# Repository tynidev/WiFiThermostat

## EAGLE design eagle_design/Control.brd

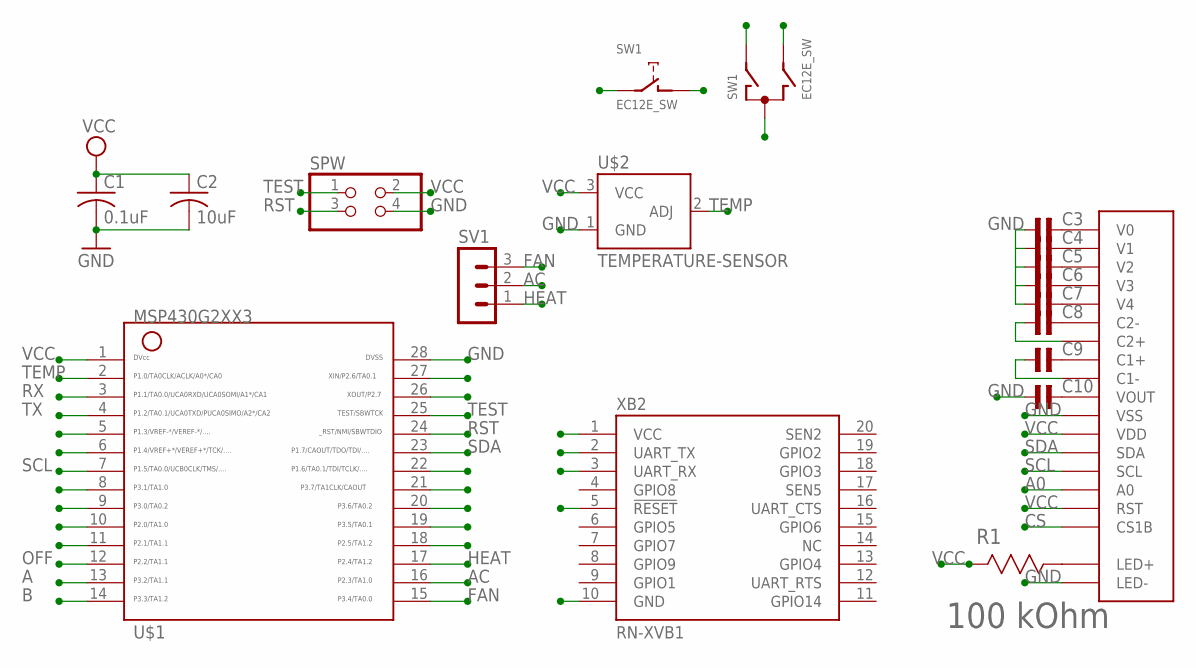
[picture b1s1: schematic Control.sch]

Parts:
C1: 0.1uF; C0603K
C2: 10uF; C0603K
C3, C4, C5, C6, C7, C8, C9, C10: C-NP-SMD-0603; C-0603
R1: 100 kOhm; RESC1608X60N
SPW: PINHD-2X2; 2X02
SV1: MA03-1
SW1: EC12E_SW; ALPS_EC12E_SW
U$1: G2XX3---PW28; PW28
U$2: TEMPERATURE-SENSOR; TO-92
U$3: NHD-C12832A1Z-FSW-FBW-3V3
XB2: RN-XVB1; XBEE

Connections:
A: SW1.B, U$1.13
A0: U$1.8, U$3.15 (A0)
AC: SV1.2, U$1.16
B: SW1.A, U$1.14
CS: U$1.9, U$3.17 (CS1B)
FAN: SV1.3, U$1.15
GND: C1.2, C2.2, C3.1, C4.1, C5.1, C6.1, C7.1, C10.1, SPW.4, SW1.C, U$1.28, U$2.1 (GND), U$3.11 (VSS), U$3.K (LED-), XB2.10 (GND)
HEAT: SV1.1, U$1.17
unnamed: C3.2, U$3.1 (V0)
unnamed: C4.2, U$3.2 (V1)
unnamed: C5.2, U$3.3 (V2)
unnamed: C6.2, U$3.4 (V3)
unnamed: C7.2, U$3.5 (V4)
unnamed: C8.2, U$3.6 (C2-)
unnamed: C9.2, U$3.8 (C1+)
unnamed: C8.1, U$3.7 (C2+)
unnamed: C10.2, U$3.10 (VOUT)
unnamed: C9.1, U$3.9 (C1-)
unnamed: R1.1 (R1), U$3.A (LED+)
OFF: SW1.E (2), U$1.12
P1_3: U$1.5
P1_4: U$1.6
P1_6: U$1.22
P2_0: U$1.10
P2_1: U$1.11
P2_5: U$1.18
P2_6: U$1.27
P2_7: U$1.26
P3_5: U$1.19
P3_6: U$1.20
P3_7: U$1.21
RST: SPW.3, U$1.24
RX: U$1.3, XB2.2 (UART_TX)
SCL: U$1.7, U$3.14 (SCL)
SDA: U$1.23, U$3.13 (SDA)
TEMP: U$1.2, U$2.2 (ADJ)
TEST: SPW.1, U$1.25
TX: U$1.4, XB2.3 (UART_RX)
VCC: C1.1, C2.1, R1.2 (R2), SPW.2, SW1.D (1), U$1.1, U$2.3 (VCC), U$3.12 (VDD), U$3.16 (RST), XB2.1 (VCC), XB2.5 (!RESET)

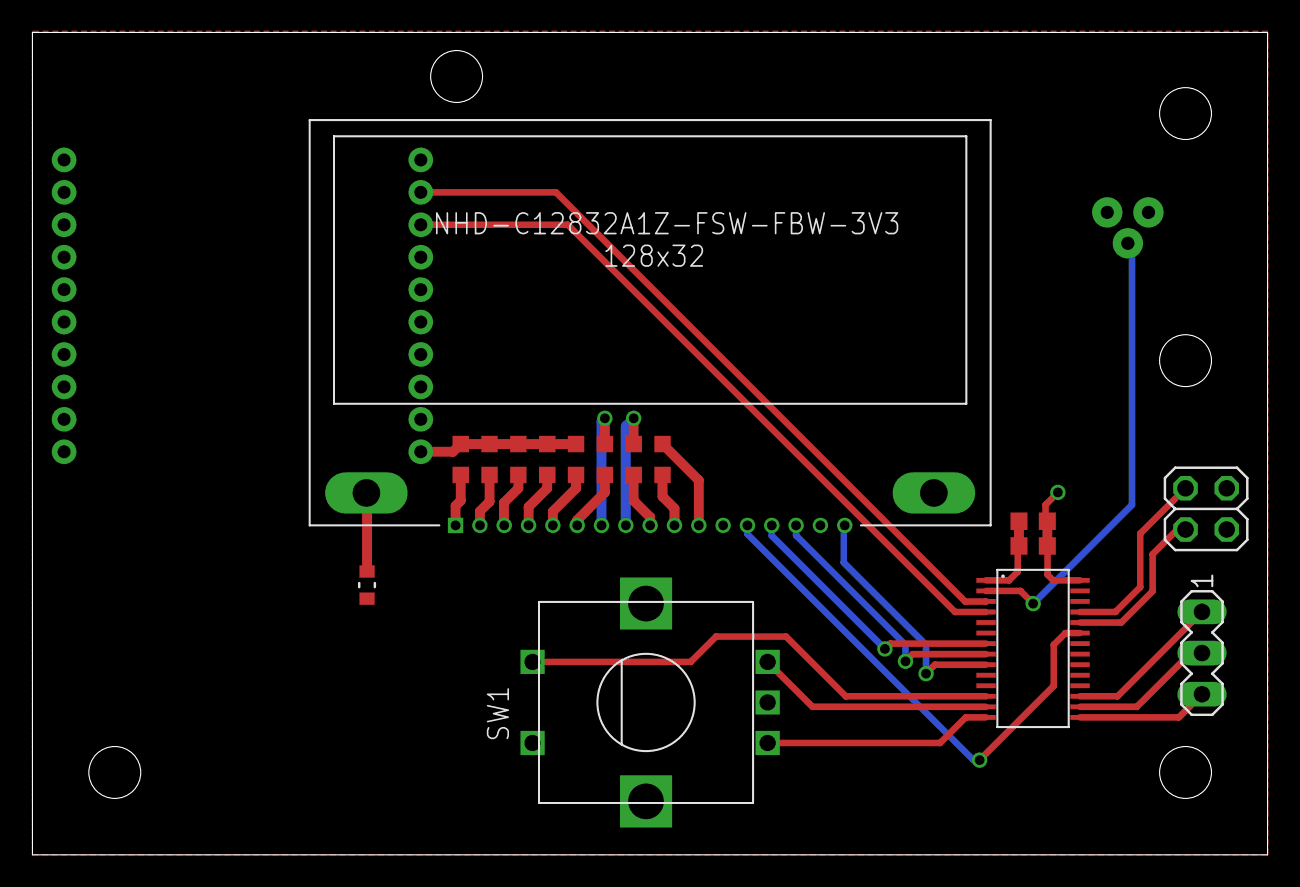
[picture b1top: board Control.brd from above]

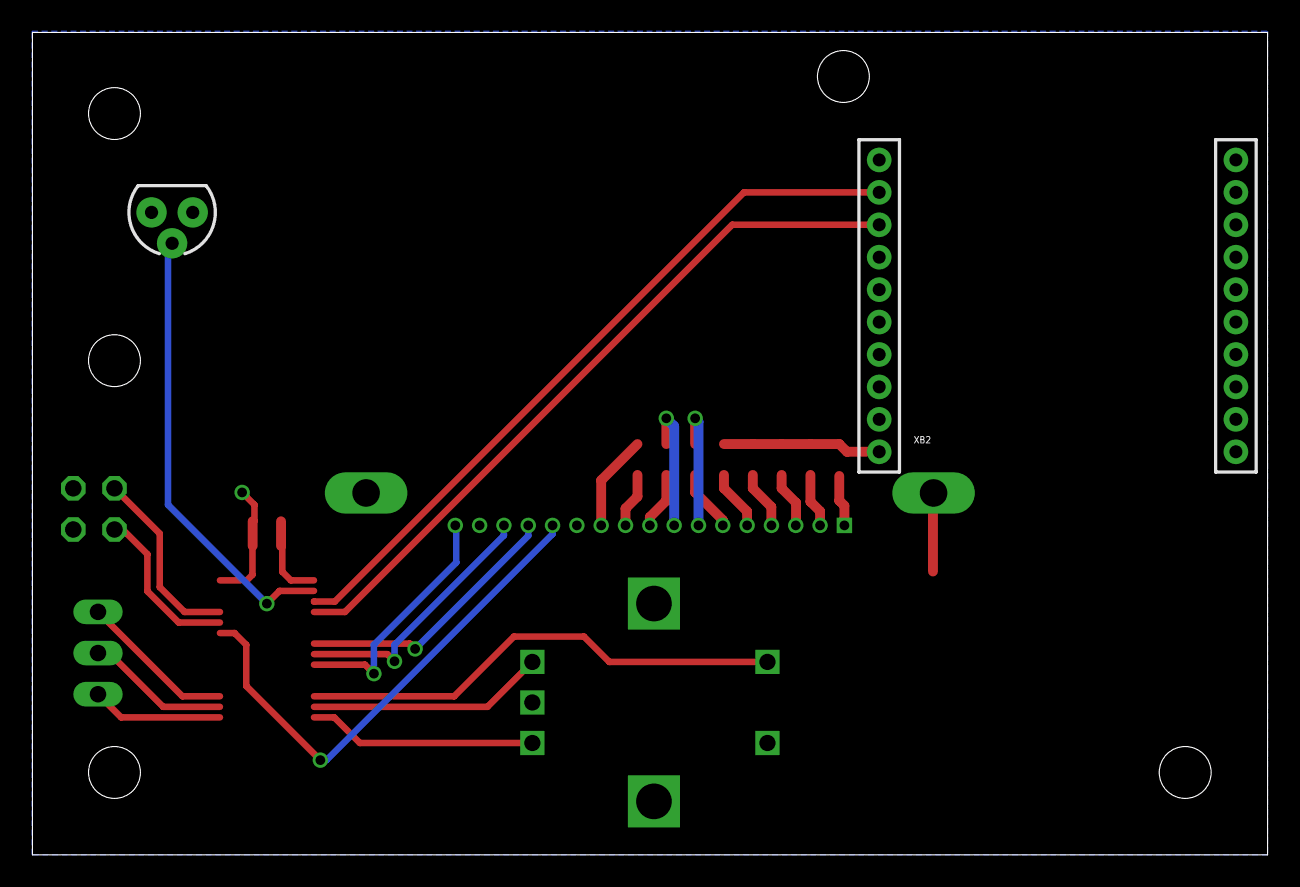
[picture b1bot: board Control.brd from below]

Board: 2 copper layers, 76.2 x 50.7 mm, 18 parts (2 on the bottom side), 28 nets.

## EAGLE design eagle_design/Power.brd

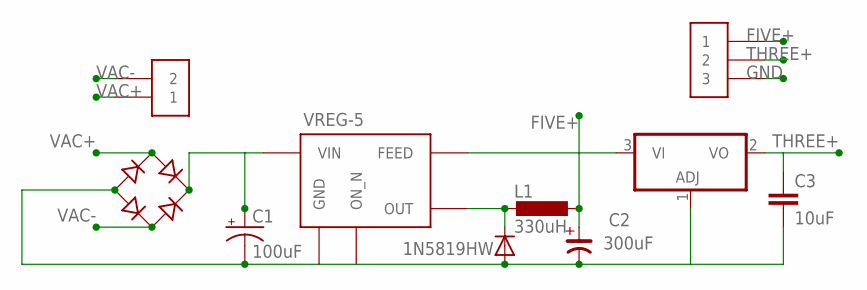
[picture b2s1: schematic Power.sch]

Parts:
B1: RECTIFIER-S80; TO-269AA
C1: 100uF; PANASONIC_G
C2: 300uF; CSV-H
C3: 10uF; C5B2.5
D8: CGRM4001-G; SOD-123_MINI-SMA
L1: 330uH; DO3316P
LT1086-3.3: 317T; TO220H
U$2: OSTTC020162
U$3: OSTTC030162
VREG-5: TL2575-05; TO-263-5

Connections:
FIVE+: C2.+, L1.2, LT1086-3.3.3 (VI), U$3.1, VREG-5.4 (FEED)
GND: B1.-, C1.-, C2.-, C3.2, D8.A, LT1086-3.3.1 (ADJ), U$3.3, VREG-5.3 (GND), VREG-5.5 (ON_N), VREG-5.TAB (GND)
unnamed: D8.C, L1.1, VREG-5.2 (OUT)
THREE+: C3.1, LT1086-3.3.2 (VO), U$3.2
VAC+: B1.AC1, U$2.1
VAC-: B1.AC2, U$2.2
VUNREG: B1.+, C1.+, VREG-5.1 (VIN)

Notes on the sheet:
VREG-5
1N5819HW

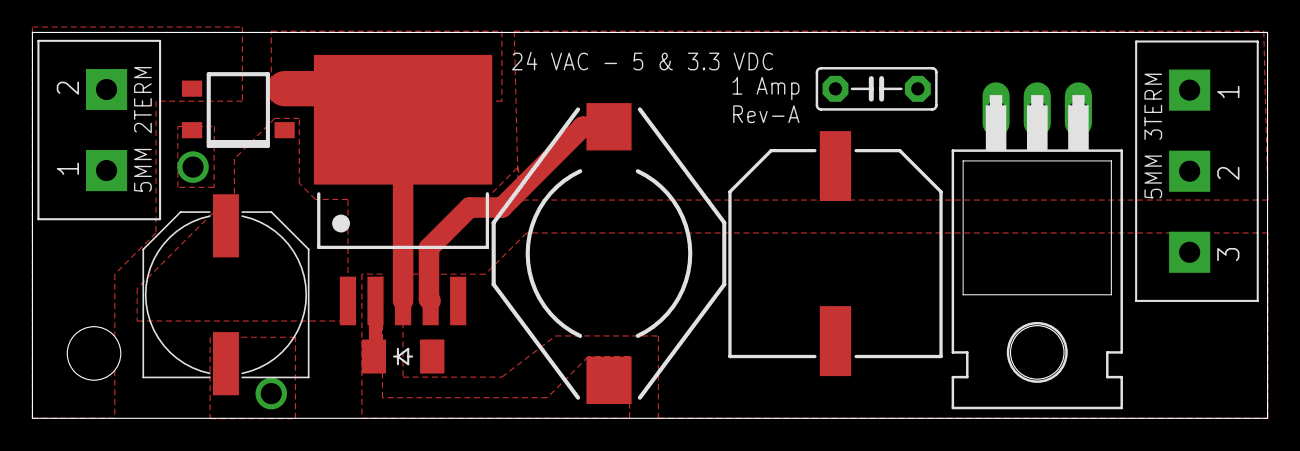
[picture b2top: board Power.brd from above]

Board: 2 copper layers, 76.2 x 23.8 mm, 10 parts (0 on the bottom side), 7 nets.

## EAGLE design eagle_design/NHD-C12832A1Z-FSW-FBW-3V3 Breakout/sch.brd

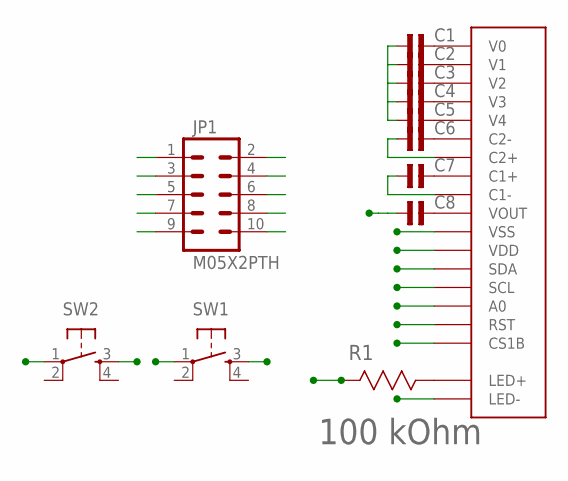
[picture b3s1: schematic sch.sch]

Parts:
C1, C2, C3, C4, C5, C6, C7, C8: C-NP-SMD-0603; C-0603
JP1: M05X2PTH; AVR_ICSP
R1: 100 kOhm; RESC1608X60N
SW1, SW2: TAC_SWITCHPTH; TACTILE-PTH
U$1: NHD-C12832A1Z-FSW-FBW-3V3

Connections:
A0: JP1.6, U$1.15 (A0)
CS1B: JP1.10, U$1.17 (CS1B)
LED+: JP1.1, R1.2 (R2)
unnamed: C1.2, U$1.1 (V0)
unnamed: C2.2, U$1.2 (V1)
unnamed: C3.2, U$1.3 (V2)
unnamed: C4.2, U$1.4 (V3)
unnamed: C5.2, U$1.5 (V4)
unnamed: C6.2, U$1.6 (C2-)
unnamed: C7.2, U$1.8 (C1+)
unnamed: C6.1, U$1.7 (C2+)
unnamed: C8.2, U$1.10 (VOUT)
unnamed: C7.1, U$1.9 (C1-)
unnamed: R1.1 (R1), U$1.A (LED+)
RST: JP1.8, U$1.16 (RST)
SCL: JP1.4, U$1.14 (SCL)
SDA: JP1.2, U$1.13 (SDA)
SW1: JP1.3, SW1.3
SW2: JP1.5, SW2.3
VDD: JP1.7, SW1.1, SW2.1, U$1.12 (VDD)
VSS: C1.1, C2.1, C3.1, C4.1, C5.1, C8.1, JP1.9, U$1.11 (VSS), U$1.K (LED-)

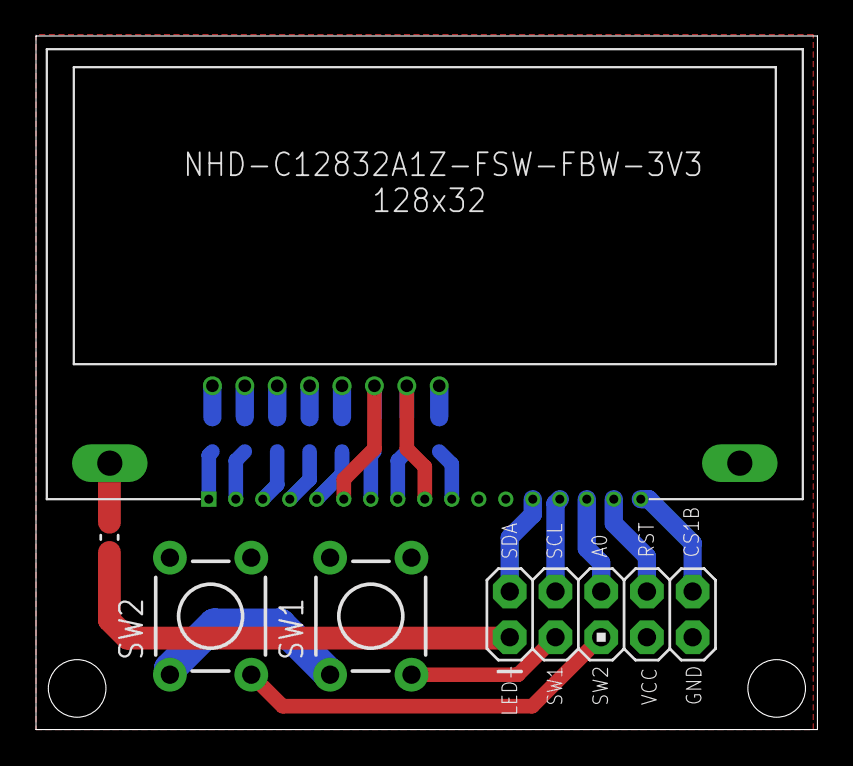
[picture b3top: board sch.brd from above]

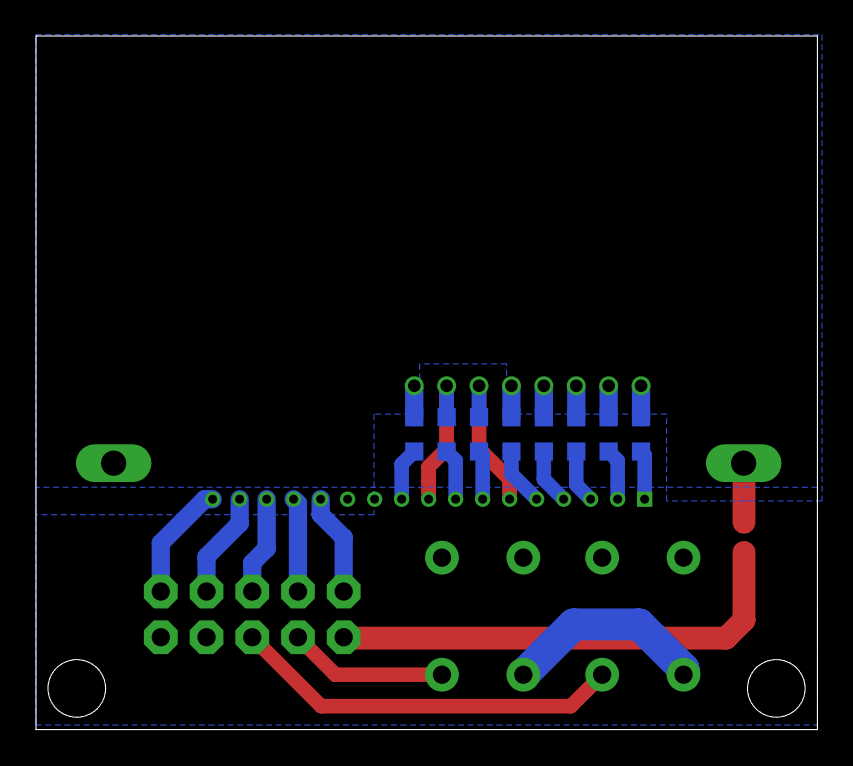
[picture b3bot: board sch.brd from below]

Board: 2 copper layers, 43.4 x 38.5 mm, 13 parts (8 on the bottom side), 21 nets.

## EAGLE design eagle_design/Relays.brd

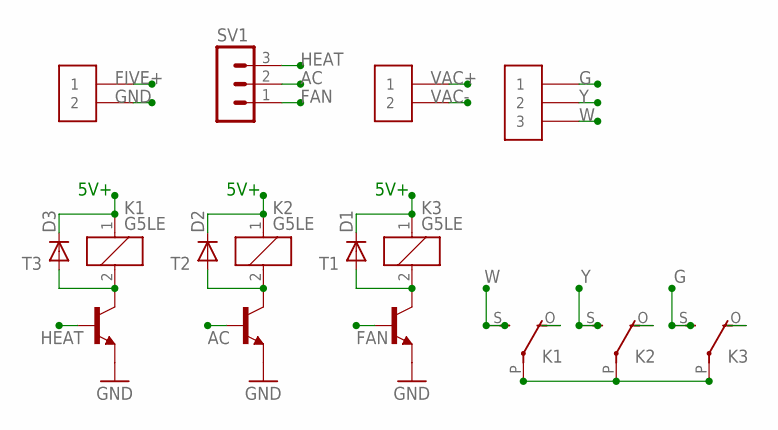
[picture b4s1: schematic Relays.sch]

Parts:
D1, D2, D3: 1N4148DO35-7; DO35-7
K1, K2, K3: G5LE
SV1: MA03-1
T1, T2, T3: 2N4401-NPN-TO92-EBC; TO92-EBC
U$4, U$5: OSTTC020162
U$6: OSTTC030162

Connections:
AC: SV1.2, T2.B
FAN: SV1.1, T1.B
FIVE+: D1.C, D2.C, D3.C, K1.1, K2.1, K3.1, U$5.1
G: K3.S, U$6.1
GND: T1.E, T2.E, T3.E, U$5.2
HEAT: SV1.3, T3.B
unnamed: D1.A, K3.2, T1.C
unnamed: D2.A, K2.2, T2.C
unnamed: D3.A, K1.2, T3.C
VAC+: K1.P, K2.P, K3.P, U$4.1
VAC-: U$4.2
W: K1.S, U$6.3
Y: K2.S, U$6.2

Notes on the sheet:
5V+

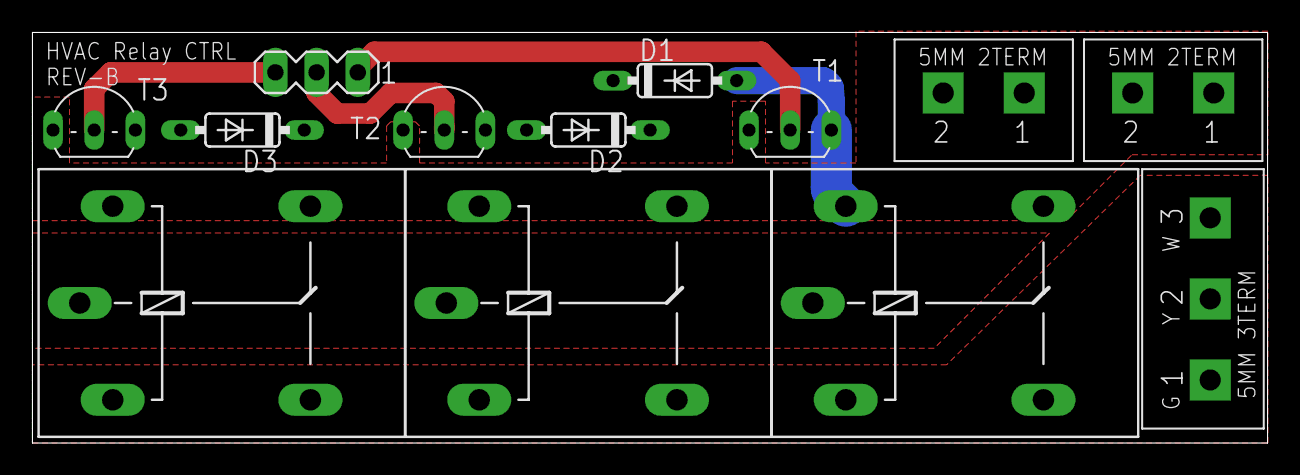
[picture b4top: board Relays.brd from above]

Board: 2 copper layers, 76.2 x 25.3 mm, 13 parts (0 on the bottom side), 12 nets.

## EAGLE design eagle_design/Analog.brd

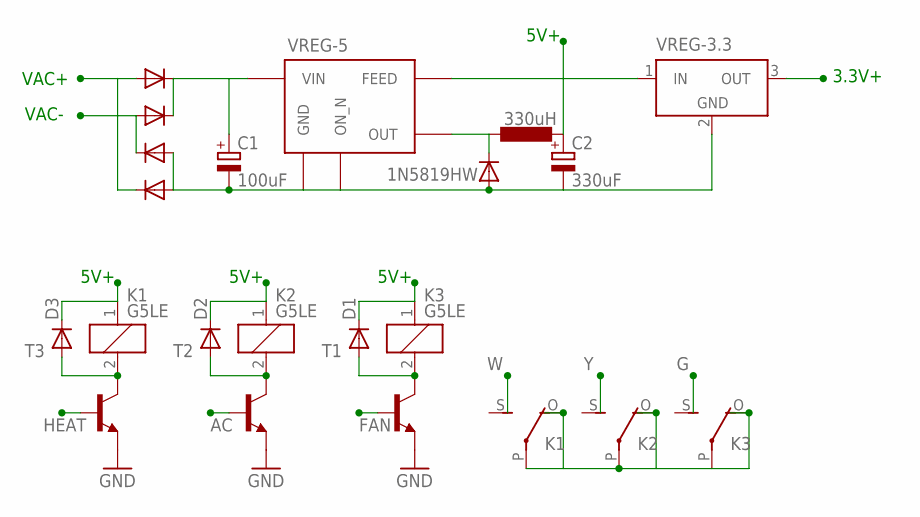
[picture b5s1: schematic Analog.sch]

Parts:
C1: 100uF; 153CLV-0405
C2: 330uF; 153CLV-0405
D1, D2, D3: 1N4148DO35-7; DO35-7
D4, D5, D6, D7: 1N4004; DO41-10
D8: CGRM4001-G; SOD-123_MINI-SMA
K1, K2, K3: G5LE
T1, T2, T3: 2N4401-NPN-TO92-EBC; TO92-EBC
VREG-3.3: LT1129CST5; SOT223
VREG-5: TL2575-05; TO-263-5

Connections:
3.3+: VREG-3.3.3 (OUT)
5V+: C2.+, D1.C, D2.C, D3.C, K1.1, K2.1, K3.1, VREG-3.3.1 (IN), VREG-5.4 (FEED)
5V-: C1.-, C2.-, D6.A, D7.A, D8.A, VREG-3.3.2 (GND), VREG-5.3 (GND), VREG-5.5 (ON_N), VREG-5.TAB (GND)
AC: T2.B
FAN: T1.B
GND: T1.E, T2.E, T3.E, VREG-3.3.4 (GND)
HEAT: T3.B
unnamed: C1.+, D4.C, D5.C, VREG-5.1 (VIN)
unnamed: D1.A, K3.2, T1.C
unnamed: D2.A, K2.2, T2.C
unnamed: D8.C, VREG-5.2 (OUT)
unnamed: D3.A, K1.2, T3.C
VAC+: D5.A, D7.C
VAC-: D4.A, D6.C, K1.O, K1.P, K2.O, K2.P, K3.O, K3.P

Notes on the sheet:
VREG-5
VAC+
VAC-
5V+
3.3V+
1N5819HW
330uH

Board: 2 copper layers, 18 parts (0 on the bottom side), 10 nets, no tracks yet.

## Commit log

2012-08-14 Added initial eagle project and schematic
2012-08-14 adding eagle temp files to gitignore
2012-08-14 corrected gitignore
2012-08-14 Added MSP430 and updated WiFly to have correct pin names
2012-08-14 added .DS_Store to gitignore
2012-08-14 added data sheet for planned msp430 processor
2012-08-14 added WiFly datasheets
2012-08-14 organizing into folders
2012-08-14 removed unnecessary project file
2012-08-25 added gitattributes file
2012-08-25 Removed C filter because indent doesn't do what I want yet
2012-08-28 added analog schematic and more data sheets
2012-08-28 removed unecessary files and added temp file to .gitignore
2012-09-11 Did some more PCB design and added some datasheets
2012-09-18 split into three boards and choose new mcu
2012-09-18 removed relays from control
2012-09-25 updated schematics
2012-09-26 made boards smaller
2012-09-26 Cleaned up boards and added script to gen gerbers
2012-10-02 more modifications
2012-11-03 added code, and modified eagle files
2012-11-15 finished control board
2012-11-15 modification of control board
2012-11-20 modified to work with msp430g2553
2012-11-26 added temp control and display
2012-11-26 style change
2012-11-26 added on/off, rearranged and debugged more
2012-11-26 Added desktop software
2012-11-28 made more changes to control code
2012-11-28 added control gui
2012-12-15 modified window gui

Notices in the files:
parts and their libraries:
SparkFun-Sensors: Licensing: CC v3.0 Share-Alike You are welcome to use this library for commercial purposes.
cap-pan40: Copyright (C) 2004, Bob Starr
rc-master: Copyright (C) 2007, Bob Starr
